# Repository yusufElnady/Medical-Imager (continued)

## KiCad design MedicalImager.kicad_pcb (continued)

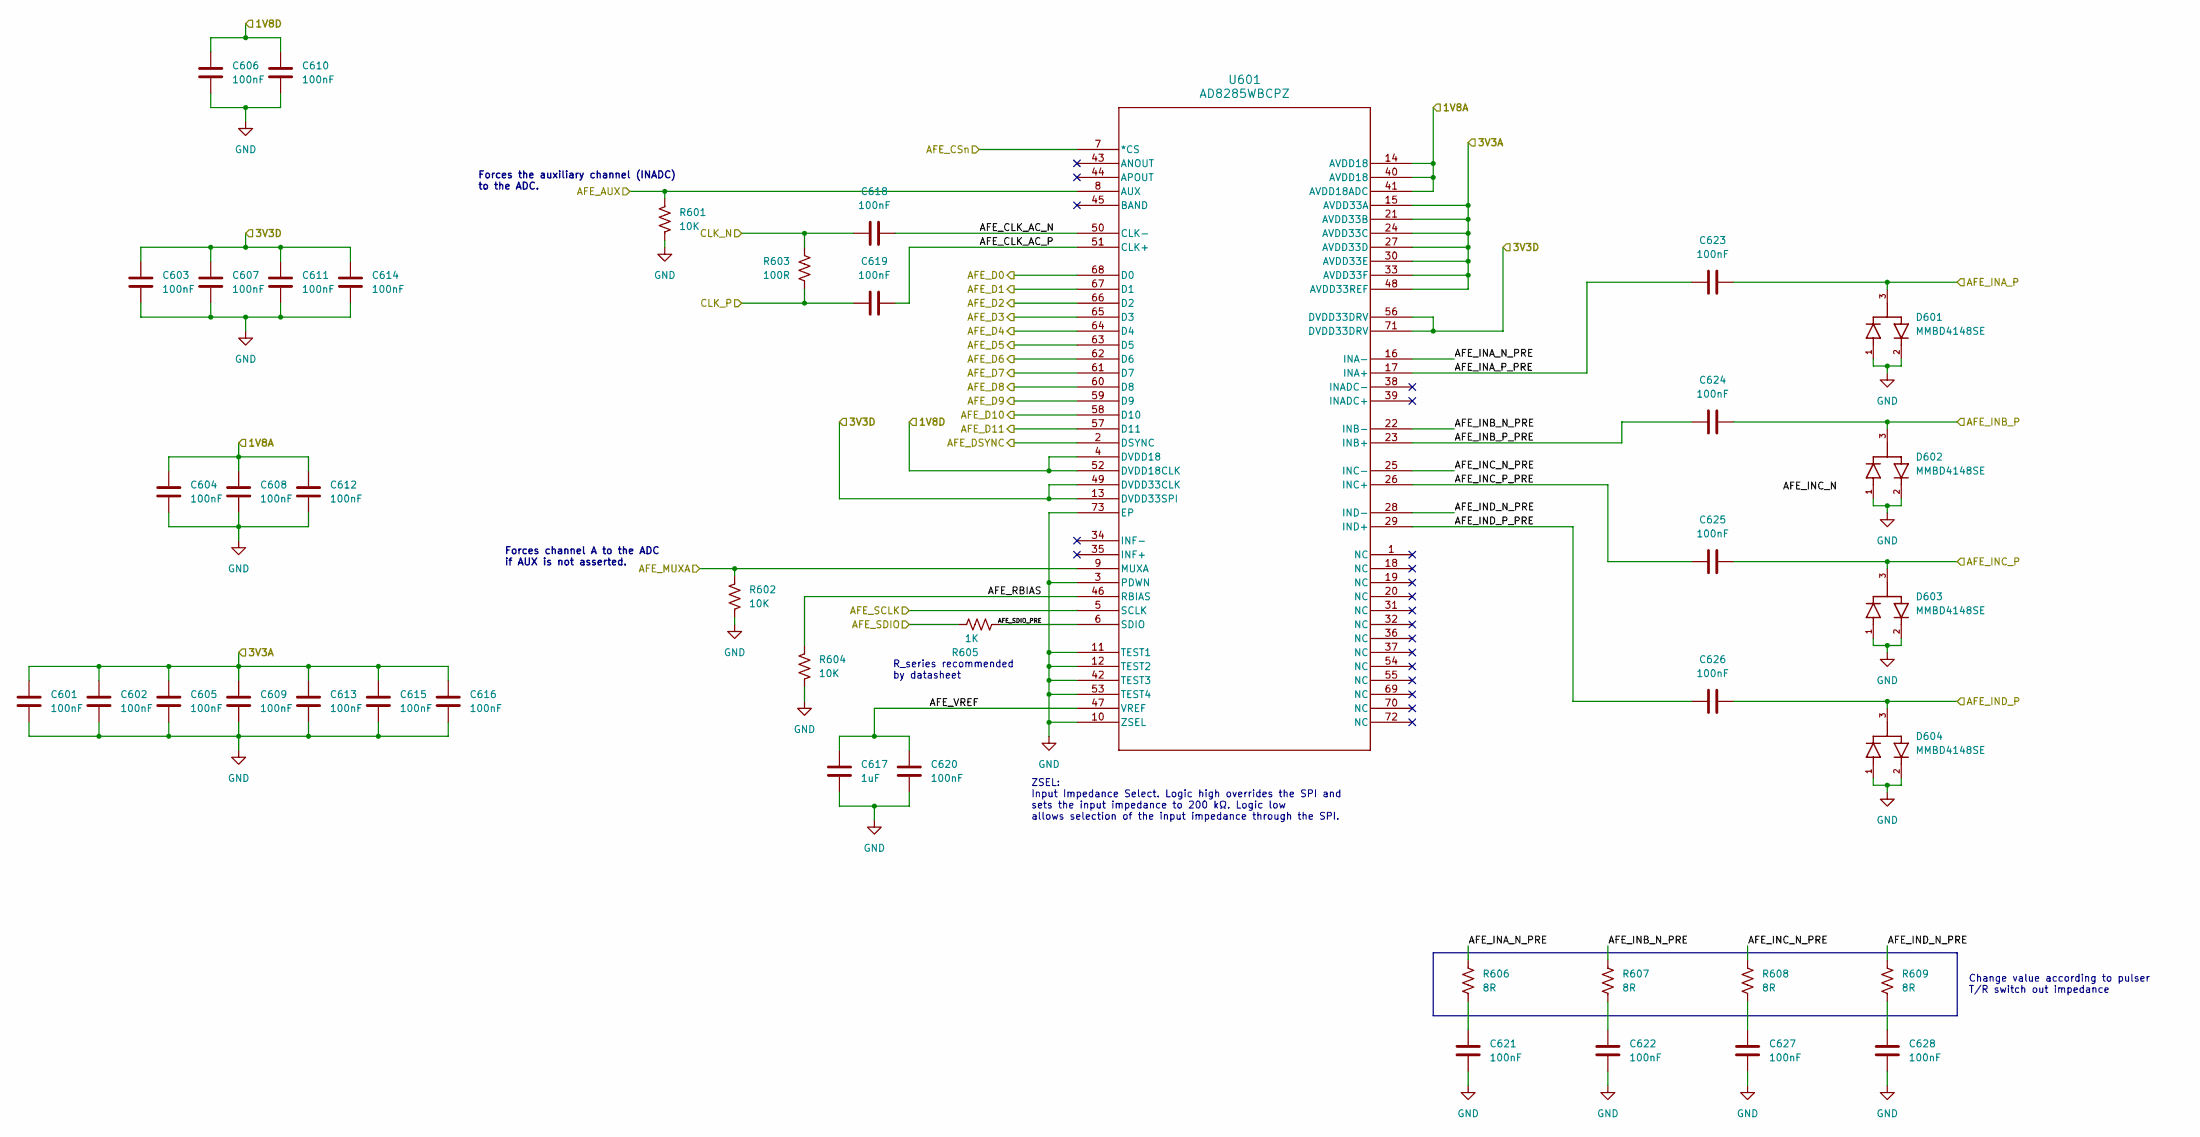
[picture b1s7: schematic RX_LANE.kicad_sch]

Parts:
C601, C602, C603, C604, C605, C606, C607, C608, C609, C610, C611, C612, C613, C614, C615, C616, C618, C619, C620, C621, C622, C623, C624, C625, C626, C627, C628: 100nF; C_0402_1005Metric
C617: 1uF; C_0402_1005Metric
D601, D602, D603, D604: MMBD4148SE; SOT95P237X112-3N; PARTREV E2001
R601, R602, R604: 10K; R_0402_1005Metric
R603: 100R; R_0402_1005Metric
R605: 1K; R_0402_1005Metric
R606, R607, R608, R609: 8R; R_0402_1005Metric
U601: AD8285WBCPZ; CP_72_5_ADI

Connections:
/RX/AFE1/AFE_CLK_AC_N: C618.2, U601.50 (CLK-)
/RX/AFE1/AFE_CLK_AC_P: C619.2, U601.51 (CLK+)
/RX/AFE1/AFE_INA_N_PRE: R606.1, U601.16 (INA-)
/RX/AFE1/AFE_INA_P_PRE: C623.2, U601.17 (INA+)
/RX/AFE1/AFE_INB_N_PRE: R607.1, U601.22 (INB-)
/RX/AFE1/AFE_INB_P_PRE: C624.2, U601.23 (INB+)
/RX/AFE1/AFE_INC_N_PRE: R608.1, U601.25 (INC-)
/RX/AFE1/AFE_INC_P_PRE: C625.2, U601.26 (INC+)
/RX/AFE1/AFE_IND_N_PRE: R609.1, U601.28 (IND-)
/RX/AFE1/AFE_IND_P_PRE: C626.2, U601.29 (IND+)
/RX/AFE1/AFE_RBIAS: R604.1, U601.46 (RBIAS)
/RX/AFE1/AFE_SDIO_PRE: R605.2, U601.6 (SDIO)
/RX/AFE1/AFE_VREF: C617.1, C620.1, U601.47 (VREF)
/RX/AFE1_AUX: R601.1, U601.8 (AUX); also elsewhere on the board
/RX/AFE1_CSn: U601.7 (*CS); also elsewhere on the board
/RX/AFE1_DSYNC: U601.2 (DSYNC); also elsewhere on the board
/RX/AFE1_MUXA: R602.1, U601.9 (MUXA); also elsewhere on the board
/RX/AFE_OUTPUTS0: U601.68 (D0); also elsewhere on the board
/RX/AFE_OUTPUTS1: U601.67 (D1); also elsewhere on the board
/RX/AFE_OUTPUTS2: U601.66 (D2); also elsewhere on the board
/RX/AFE_OUTPUTS3: U601.65 (D3); also elsewhere on the board
/RX/AFE_OUTPUTS4: U601.64 (D4); also elsewhere on the board
/RX/AFE_OUTPUTS5: U601.63 (D5); also elsewhere on the board
/RX/AFE_OUTPUTS6: U601.62 (D6); also elsewhere on the board
/RX/AFE_OUTPUTS7: U601.61 (D7); also elsewhere on the board
/RX/AFE_OUTPUTS8: U601.60 (D8); also elsewhere on the board
/RX/AFE_OUTPUTS9: U601.59 (D9); also elsewhere on the board
/RX/AFE_OUTPUTS10: U601.58 (D10); also elsewhere on the board
/RX/AFE_OUTPUTS11: U601.57 (D11); also elsewhere on the board
/RX/AFE_SCLK: U601.5 (SCLK); also elsewhere on the board
/RX/AFE_SDIO: R605.1; also elsewhere on the board
/RX/CLKOUT_B1_N: C618.1, R603.1; also elsewhere on the board
/RX/CLKOUT_B1_P: C619.1, R603.2; also elsewhere on the board
/RX/TR_OUT0: C623.1, D601.3; also elsewhere on the board
/RX/TR_OUT1: C624.1, D602.3; also elsewhere on the board
/RX/TR_OUT2: C625.1, D603.3; also elsewhere on the board
/RX/TR_OUT3: C626.1, D604.3; also elsewhere on the board
AFE1_1V8A: C604.1, C608.1, C612.1, U601.14 (AVDD18), U601.40 (AVDD18), U601.41 (AVDD18ADC); also elsewhere on the board
AFE1_1V8D: C606.1, C610.1, U601.4 (DVDD18), U601.52 (DVDD18CLK); also elsewhere on the board
AFE1_3V3A: C601.1, C602.1, C605.1, C609.1, C613.1, C615.1, C616.1, U601.15 (AVDD33A), U601.21 (AVDD33B), U601.24 (AVDD33C), U601.27 (AVDD33D), U601.30 (AVDD33E), U601.33 (AVDD33F), U601.48 (AVDD33REF); also elsewhere on the board
AFE1_3V3D: C603.1, C607.1, C611.1, C614.1, U601.13 (DVDD33SPI), U601.49 (DVDD33CLK), U601.56 (DVDD33DRV), U601.71 (DVDD33DRV); also elsewhere on the board
GND: C601.2, C602.2, C603.2, C604.2, C605.2, C606.2, C607.2, C608.2, C609.2, C610.2, C611.2, C612.2, C613.2, C614.2, C615.2, C616.2, C617.2, C620.2, C621.2, C622.2, C627.2, C628.2, D601.1, D601.2, D602.1, D602.2, D603.1, D603.2, D604.1, D604.2, R601.2, R602.2, R604.2, U601.3 (PDWN), U601.10 (ZSEL), U601.11 (TEST1), U601.12 (TEST2), U601.42 (TEST3), U601.53 (TEST4), U601.73 (EP); also elsewhere on the board
unnamed: C621.1, R606.2
unnamed: C622.1, R607.2
unnamed: C627.1, R608.2
unnamed: C628.1, R609.2

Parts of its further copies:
C701, C702, C703, C704, C705, C706, C707, C708, C709, C710, C711, C712, C713, C714, C715, C716, C718, C719, C720, C721, C722, C723, C724, C725, C726, C727, C728, C801, C802, C803, C804, C805, C806, C807, C808, C809, C810, C811, C812, C813, C814, C815, C816, C818, C819, C820, C821, C822, C823, C824, C825, C826, C827, C828, C901, C902, C903, C904, C905, C906, C907, C908, C909, C910, C911, C912, C913, C914, C915, C916, C918, C919, C920, C921, C922, C923, C924, C925, C926, C927, C928: 100nF; C_0402_1005Metric
C717, C817, C917: 1uF; C_0402_1005Metric
D701, D702, D703, D704, D801, D802, D803, D804, D901, D902, D903, D904: MMBD4148SE; SOT95P237X112-3N; PARTREV E2001
R701, R702, R704, R801, R802, R804, R901, R902, R904: 10K; R_0402_1005Metric
R703, R803, R903: 100R; R_0402_1005Metric
R705, R805, R905: 1K; R_0402_1005Metric
R706, R707, R708, R709, R806, R807, R808, R809, R906, R907, R908, R909: 8R; R_0402_1005Metric
U701, U801, U901: AD8285WBCPZ; CP_72_5_ADI

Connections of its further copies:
/RX/AFE2/AFE_CLK_AC_N: C718.2, U701.50 (CLK-)
/RX/AFE2/AFE_CLK_AC_P: C719.2, U701.51 (CLK+)
/RX/AFE2/AFE_INA_N_PRE: R706.1, U701.16 (INA-)
/RX/AFE2/AFE_INA_P_PRE: C723.2, U701.17 (INA+)
/RX/AFE2/AFE_INB_N_PRE: R707.1, U701.22 (INB-)
/RX/AFE2/AFE_INB_P_PRE: C724.2, U701.23 (INB+)
/RX/AFE2/AFE_INC_N_PRE: R708.1, U701.25 (INC-)
/RX/AFE2/AFE_INC_P_PRE: C725.2, U701.26 (INC+)
/RX/AFE2/AFE_IND_N_PRE: R709.1, U701.28 (IND-)
/RX/AFE2/AFE_IND_P_PRE: C726.2, U701.29 (IND+)
/RX/AFE2/AFE_RBIAS: R704.1, U701.46 (RBIAS)
/RX/AFE2/AFE_SDIO_PRE: R705.2, U701.6 (SDIO)
/RX/AFE2/AFE_VREF: C717.1, C720.1, U701.47 (VREF)
/RX/AFE2_AUX: R701.1, U701.8 (AUX); also elsewhere on the board
/RX/AFE2_CSn: U701.7 (*CS); also elsewhere on the board
/RX/AFE2_DSYNC: U701.2 (DSYNC); also elsewhere on the board
/RX/AFE2_MUXA: R702.1, U701.9 (MUXA); also elsewhere on the board
/RX/AFE3/AFE_CLK_AC_N: C818.2, U801.50 (CLK-)
/RX/AFE3/AFE_CLK_AC_P: C819.2, U801.51 (CLK+)
/RX/AFE3/AFE_INA_N_PRE: R806.1, U801.16 (INA-)
/RX/AFE3/AFE_INA_P_PRE: C823.2, U801.17 (INA+)
/RX/AFE3/AFE_INB_N_PRE: R807.1, U801.22 (INB-)
/RX/AFE3/AFE_INB_P_PRE: C824.2, U801.23 (INB+)
/RX/AFE3/AFE_INC_N_PRE: R808.1, U801.25 (INC-)
/RX/AFE3/AFE_INC_P_PRE: C825.2, U801.26 (INC+)
/RX/AFE3/AFE_IND_N_PRE: R809.1, U801.28 (IND-)
/RX/AFE3/AFE_IND_P_PRE: C826.2, U801.29 (IND+)
/RX/AFE3/AFE_RBIAS: R804.1, U801.46 (RBIAS)
/RX/AFE3/AFE_SDIO_PRE: R805.2, U801.6 (SDIO)
/RX/AFE3/AFE_VREF: C817.1, C820.1, U801.47 (VREF)
/RX/AFE3_AUX: R801.1, U801.8 (AUX); also elsewhere on the board
/RX/AFE3_CSn: U801.7 (*CS); also elsewhere on the board
/RX/AFE3_DSYNC: U801.2 (DSYNC); also elsewhere on the board
/RX/AFE3_MUXA: R802.1, U801.9 (MUXA); also elsewhere on the board
/RX/AFE4/AFE_CLK_AC_N: C918.2, U901.50 (CLK-)
/RX/AFE4/AFE_CLK_AC_P: C919.2, U901.51 (CLK+)
/RX/AFE4/AFE_INA_N_PRE: R906.1, U901.16 (INA-)
/RX/AFE4/AFE_INA_P_PRE: C923.2, U901.17 (INA+)
/RX/AFE4/AFE_INB_N_PRE: R907.1, U901.22 (INB-)
/RX/AFE4/AFE_INB_P_PRE: C924.2, U901.23 (INB+)
/RX/AFE4/AFE_INC_N_PRE: R908.1, U901.25 (INC-)
/RX/AFE4/AFE_INC_P_PRE: C925.2, U901.26 (INC+)
/RX/AFE4/AFE_IND_N_PRE: R909.1, U901.28 (IND-)
/RX/AFE4/AFE_IND_P_PRE: C926.2, U901.29 (IND+)
/RX/AFE4/AFE_RBIAS: R904.1, U901.46 (RBIAS)
/RX/AFE4/AFE_SDIO_PRE: R905.2, U901.6 (SDIO)
/RX/AFE4/AFE_VREF: C917.1, C920.1, U901.47 (VREF)
/RX/AFE4_AUX: R901.1, U901.8 (AUX); also elsewhere on the board
/RX/AFE4_CSn: U901.7 (*CS); also elsewhere on the board
/RX/AFE4_DSYNC: U901.2 (DSYNC); also elsewhere on the board
/RX/AFE4_MUXA: R902.1, U901.9 (MUXA); also elsewhere on the board
/RX/AFE_OUTPUTS12: U701.68 (D0); also elsewhere on the board
/RX/AFE_OUTPUTS13: U701.67 (D1); also elsewhere on the board
/RX/AFE_OUTPUTS14: U701.66 (D2); also elsewhere on the board
/RX/AFE_OUTPUTS15: U701.65 (D3); also elsewhere on the board
/RX/AFE_OUTPUTS16: U701.64 (D4); also elsewhere on the board
/RX/AFE_OUTPUTS17: U701.63 (D5); also elsewhere on the board
/RX/AFE_OUTPUTS18: U701.62 (D6); also elsewhere on the board
/RX/AFE_OUTPUTS19: U701.61 (D7); also elsewhere on the board
/RX/AFE_OUTPUTS20: U701.60 (D8); also elsewhere on the board
/RX/AFE_OUTPUTS21: U701.59 (D9); also elsewhere on the board
/RX/AFE_OUTPUTS22: U701.58 (D10); also elsewhere on the board
/RX/AFE_OUTPUTS23: U701.57 (D11); also elsewhere on the board
/RX/AFE_OUTPUTS24: U801.68 (D0); also elsewhere on the board
/RX/AFE_OUTPUTS25: U801.67 (D1); also elsewhere on the board
/RX/AFE_OUTPUTS26: U801.66 (D2); also elsewhere on the board
/RX/AFE_OUTPUTS27: U801.65 (D3); also elsewhere on the board
/RX/AFE_OUTPUTS28: U801.64 (D4); also elsewhere on the board
/RX/AFE_OUTPUTS29: U801.63 (D5); also elsewhere on the board
/RX/AFE_OUTPUTS30: U801.62 (D6); also elsewhere on the board
/RX/AFE_OUTPUTS31: U801.61 (D7); also elsewhere on the board
/RX/AFE_OUTPUTS32: U801.60 (D8); also elsewhere on the board
/RX/AFE_OUTPUTS33: U801.59 (D9); also elsewhere on the board
/RX/AFE_OUTPUTS34: U801.58 (D10); also elsewhere on the board
/RX/AFE_OUTPUTS35: U801.57 (D11); also elsewhere on the board
/RX/AFE_OUTPUTS36: U901.68 (D0); also elsewhere on the board
/RX/AFE_OUTPUTS37: U901.67 (D1); also elsewhere on the board
/RX/AFE_OUTPUTS38: U901.66 (D2); also elsewhere on the board
/RX/AFE_OUTPUTS39: U901.65 (D3); also elsewhere on the board
/RX/AFE_OUTPUTS40: U901.64 (D4); also elsewhere on the board
/RX/AFE_OUTPUTS41: U901.63 (D5); also elsewhere on the board
/RX/AFE_OUTPUTS42: U901.62 (D6); also elsewhere on the board
/RX/AFE_OUTPUTS43: U901.61 (D7); also elsewhere on the board
/RX/AFE_OUTPUTS44: U901.60 (D8); also elsewhere on the board
/RX/AFE_OUTPUTS45: U901.59 (D9); also elsewhere on the board
/RX/AFE_OUTPUTS46: U901.58 (D10); also elsewhere on the board
/RX/AFE_OUTPUTS47: U901.57 (D11); also elsewhere on the board
/RX/AFE_SCLK: U701.5 (SCLK), U801.5 (SCLK), U901.5 (SCLK); also elsewhere on the board
/RX/AFE_SDIO: R705.1, R805.1, R905.1; also elsewhere on the board
/RX/CLKOUT_A0_N: C918.1, R903.1; also elsewhere on the board
/RX/CLKOUT_A0_P: C919.1, R903.2; also elsewhere on the board
/RX/CLKOUT_A1_N: C818.1, R803.1; also elsewhere on the board
/RX/CLKOUT_A1_P: C819.1, R803.2; also elsewhere on the board
/RX/CLKOUT_B0_N: C718.1, R703.1; also elsewhere on the board
/RX/CLKOUT_B0_P: C719.1, R703.2; also elsewhere on the board
/RX/TR_OUT4: C723.1, D701.3; also elsewhere on the board
/RX/TR_OUT5: C724.1, D702.3; also elsewhere on the board
/RX/TR_OUT6: C725.1, D703.3; also elsewhere on the board
/RX/TR_OUT7: C726.1, D704.3; also elsewhere on the board
/RX/TR_OUT8: C823.1, D801.3; also elsewhere on the board
/RX/TR_OUT9: C824.1, D802.3; also elsewhere on the board
/RX/TR_OUT10: C825.1, D803.3; also elsewhere on the board
/RX/TR_OUT11: C826.1, D804.3; also elsewhere on the board
/RX/TR_OUT12: C923.1, D901.3; also elsewhere on the board
/RX/TR_OUT13: C924.1, D902.3; also elsewhere on the board
/RX/TR_OUT14: C925.1, D903.3; also elsewhere on the board
/RX/TR_OUT15: C926.1, D904.3; also elsewhere on the board
AFE1_1V8D: C706.1, C710.1, U701.4 (DVDD18), U701.52 (DVDD18CLK); also elsewhere on the board
AFE1_3V3D: C703.1, C707.1, C711.1, C714.1, U701.13 (DVDD33SPI), U701.49 (DVDD33CLK), U701.56 (DVDD33DRV), U701.71 (DVDD33DRV); also elsewhere on the board
AFE2_1V8A: C704.1, C708.1, C712.1, U701.14 (AVDD18), U701.40 (AVDD18), U701.41 (AVDD18ADC); also elsewhere on the board
AFE2_3V3A: C701.1, C702.1, C705.1, C709.1, C713.1, C715.1, C716.1, U701.15 (AVDD33A), U701.21 (AVDD33B), U701.24 (AVDD33C), U701.27 (AVDD33D), U701.30 (AVDD33E), U701.33 (AVDD33F), U701.48 (AVDD33REF); also elsewhere on the board
AFE3_1V8A: C804.1, C808.1, C812.1, U801.14 (AVDD18), U801.40 (AVDD18), U801.41 (AVDD18ADC); also elsewhere on the board
AFE3_1V8D: C806.1, C810.1, C906.1, C910.1, U801.4 (DVDD18), U801.52 (DVDD18CLK), U901.4 (DVDD18), U901.52 (DVDD18CLK); also elsewhere on the board
AFE3_3V3A: C801.1, C802.1, C805.1, C809.1, C813.1, C815.1, C816.1, U801.15 (AVDD33A), U801.21 (AVDD33B), U801.24 (AVDD33C), U801.27 (AVDD33D), U801.30 (AVDD33E), U801.33 (AVDD33F), U801.48 (AVDD33REF); also elsewhere on the board
AFE3_3V3D: C803.1, C807.1, C811.1, C814.1, C903.1, C907.1, C911.1, C914.1, U801.13 (DVDD33SPI), U801.49 (DVDD33CLK), U801.56 (DVDD33DRV), U801.71 (DVDD33DRV), U901.13 (DVDD33SPI), U901.49 (DVDD33CLK), U901.56 (DVDD33DRV), U901.71 (DVDD33DRV); also elsewhere on the board
AFE4_1V8A: C904.1, C908.1, C912.1, U901.14 (AVDD18), U901.40 (AVDD18), U901.41 (AVDD18ADC); also elsewhere on the board
AFE4_3V3A: C901.1, C902.1, C905.1, C909.1, C913.1, C915.1, C916.1, U901.15 (AVDD33A), U901.21 (AVDD33B), U901.24 (AVDD33C), U901.27 (AVDD33D), U901.30 (AVDD33E), U901.33 (AVDD33F), U901.48 (AVDD33REF); also elsewhere on the board
GND: C701.2, C702.2, C703.2, C704.2, C705.2, C706.2, C707.2, C708.2, C709.2, C710.2, C711.2, C712.2, C713.2, C714.2, C715.2, C716.2, C717.2, C720.2, C721.2, C722.2, C727.2, C728.2, C801.2, C802.2, C803.2, C804.2, C805.2, C806.2, C807.2, C808.2, C809.2, C810.2, C811.2, C812.2, C813.2, C814.2, C815.2, C816.2, C817.2, C820.2, C821.2, C822.2, C827.2, C828.2, C901.2, C902.2, C903.2, C904.2, C905.2, C906.2, C907.2, C908.2, C909.2, C910.2, C911.2, C912.2, C913.2, C914.2, C915.2, C916.2, C917.2, C920.2, C921.2, C922.2, C927.2, C928.2, D701.1, D701.2, D702.1, D702.2, D703.1, D703.2, D704.1, D704.2, D801.1, D801.2, D802.1, D802.2, D803.1, D803.2, D804.1, D804.2, D901.1, D901.2, D902.1, D902.2, D903.1, D903.2, D904.1, D904.2, R701.2, R702.2, R704.2, R801.2, R802.2, R804.2, R901.2, R902.2, R904.2, U701.3 (PDWN), U701.10 (ZSEL), U701.11 (TEST1), U701.12 (TEST2), U701.42 (TEST3), U701.53 (TEST4), U701.73 (EP), U801.3 (PDWN), U801.10 (ZSEL), U801.11 (TEST1), U801.12 (TEST2), U801.42 (TEST3), U801.53 (TEST4), U801.73 (EP), U901.3 (PDWN), U901.10 (ZSEL), U901.11 (TEST1), U901.12 (TEST2), U901.42 (TEST3), U901.53 (TEST4), U901.73 (EP); also elsewhere on the board
unnamed: C721.1, R706.2
unnamed: C722.1, R707.2
unnamed: C727.1, R708.2
unnamed: C728.1, R709.2
unnamed: C821.1, R806.2
unnamed: C822.1, R807.2
unnamed: C827.1, R808.2
unnamed: C828.1, R809.2
unnamed: C921.1, R906.2
unnamed: C922.1, R907.2
unnamed: C927.1, R908.2
unnamed: C928.1, R909.2

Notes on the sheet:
ZSEL: Input Impedance Select. Logic high overrides the SPI and sets the input impedance to 200 kΩ. Logic low allows selection of the input impedance through the SPI.
Forces channel A to the ADC if AUX is not asserted.
R_series recommended by datasheet
Change value according to pulser T/R switch out impedance
Forces the auxiliary channel (INADC) to the ADC.

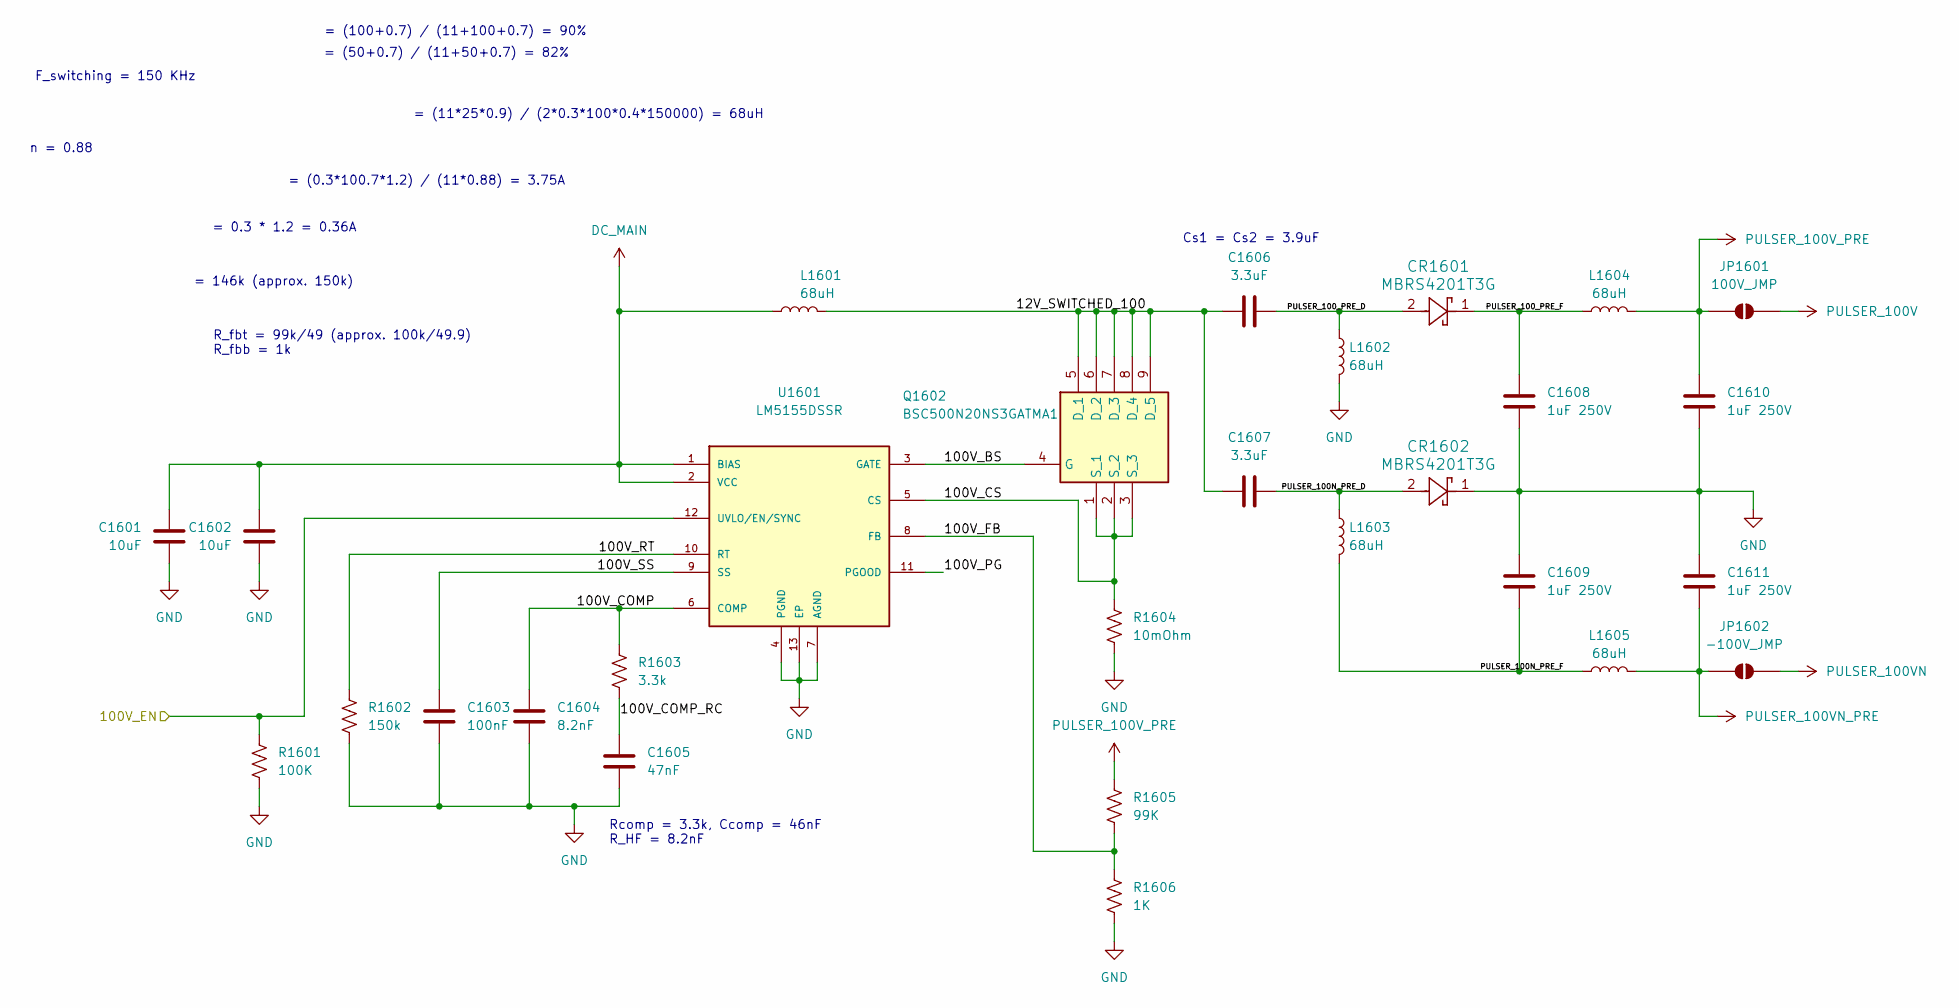
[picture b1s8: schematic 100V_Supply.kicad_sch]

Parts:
C1601, C1602: 10uF; C_0805_2012Metric
C1603: 100nF; C_0402_1005Metric
C1604: 8.2nF; C_0402_1005Metric
C1605: 47nF; C_0402_1005Metric
C1606, C1607: 3.3uF; C_2220_5750Metric
C1608, C1609, C1610, C1611: 1uF 250V; C_1812_4532Metric
CR1601, CR1602: MBRS4201T3G; SDO_SMC-2_403AC-B_OSI
JP1601: 100V_JMP; SolderJumper-2_P1.3mm_Open_TrianglePad1.0x1.5mm
JP1602: -100V_JMP; SolderJumper-2_P1.3mm_Open_TrianglePad1.0x1.5mm
L1601: 68uH; L_Panasonic_PCC-M0854M
L1602, L1603, L1604, L1605: 68uH; L_Cenker_CKCS4018
Q1602: BSC500N20NS3GATMA1; Manufacturer_Part_Number BSC500N20NS3GATMA1; Mouser Part Number 726-BSC500N20NS3GATM
R1601: 100K; R_0402_1005Metric
R1602: 150k; R_0402_1005Metric
R1603: 3.3k; R_0402_1005Metric
R1604: 10mOhm; R_0603_1608Metric
R1605: 99K; R_0402_1005Metric
R1606: 1K; R_0402_1005Metric
U1601: LM5155DSSR; IC_LM5155DSSR; PARTREV E

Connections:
/Power/100V_EN: R1601.1, U1601.12 (UVLO/EN/SYNC); also elsewhere on the board
/Power/100V_SUPPLY/12V_SWITCHED_100: C1606.1, C1607.1, L1601.1, Q1602.5 (D_1), Q1602.6 (D_2), Q1602.7 (D_3), Q1602.8 (D_4), Q1602.9 (D_5)
/Power/100V_SUPPLY/100V_BS: Q1602.4 (G), U1601.3 (GATE)
/Power/100V_SUPPLY/100V_COMP: C1604.1, R1603.1, U1601.6 (COMP)
/Power/100V_SUPPLY/100V_COMP_RC: C1605.1, R1603.2
/Power/100V_SUPPLY/100V_CS: Q1602.1 (S_1), Q1602.2 (S_2), Q1602.3 (S_3), R1604.2, U1601.5 (CS)
/Power/100V_SUPPLY/100V_FB: R1605.2, R1606.1, U1601.8 (FB)
/Power/100V_SUPPLY/100V_PG: U1601.11 (PGOOD)
/Power/100V_SUPPLY/100V_RT: R1602.1, U1601.10 (RT)
/Power/100V_SUPPLY/100V_SS: C1603.2, U1601.9 (SS)
/Power/100V_SUPPLY/PULSER_100N_PRE_D: C1607.2, CR1602.2, L1603.1
/Power/100V_SUPPLY/PULSER_100N_PRE_F: C1609.2, L1603.2, L1605.1
/Power/100V_SUPPLY/PULSER_100_PRE_D: C1606.2, CR1601.2, L1602.1
/Power/100V_SUPPLY/PULSER_100_PRE_F: C1608.1, CR1601.1, L1604.1
DC_MAIN: C1601.1, C1602.1, L1601.2, U1601.1 (BIAS), U1601.2 (VCC); also elsewhere on the board
GND: C1601.2, C1602.2, C1603.1, C1604.2, C1605.2, C1608.2, C1609.1, C1610.2, C1611.1, CR1602.1, L1602.2, R1601.2, R1602.2, R1604.1, R1606.2, U1601.4 (PGND), U1601.7 (AGND), U1601.13 (EP); also elsewhere on the board
PULSER_100V: JP1601.2 (B); also elsewhere on the board
PULSER_100VN: JP1602.2 (B); also elsewhere on the board
PULSER_100VN_PRE: C1611.2, JP1602.1 (A), L1605.2
PULSER_100V_PRE: C1610.1, JP1601.1 (A), L1604.2, R1605.1

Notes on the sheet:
F_switching = 150 KHz
Cs1 = Cs2 = 3.9uF
= (100+0.7) / (11+100+0.7) = 90%
Rcomp = 3.3k, Ccomp = 46nF R_HF = 8.2nF
= 146k (approx. 150k)
n = 0.88
= (11*25*0.9) / (2*0.3*100*0.4*150000) = 68uH
= 0.3 * 1.2 = 0.36A
R_fbt = 99k/49 (approx. 100k/49.9) R_fbb = 1k
= (50+0.7) / (11+50+0.7) = 82%
= (0.3*100.7*1.2) / (11*0.88) = 3.75A

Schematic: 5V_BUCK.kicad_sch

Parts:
C1901, C1913: 4.7uF; C_0805_2012Metric
C1902, C1915: 470nF; C_0402_1005Metric
C1907, C1908, C1910: 47uF; C_0805_2012Metric
C1911: 100nF; C_0402_1005Metric
C1912: 1pF; C_0402_1005Metric
C1914: 1uF; C_0402_1005Metric
L1902: 8.2uH; L_10.4x10.4_H4.8
R1901, R1907: 100K; R_0402_1005Metric
R1906: 32.4k; R_0402_1005Metric
R1908: 24.9K; R_0402_1005Metric
U1902: LM61460AANRJRR; IC_LM61460AANRJRR; MPN LM61460AANRJRR

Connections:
/Power/SOM_5V/BUCK_BS: C1911.1, U1902.13 (RBOOT), U1902.14 (CBOOT)
/Power/SOM_5V/BUCK_FB: C1912.2, R1907.2, R1908.1, U1902.4 (FB)
/Power/SOM_5V/BUCK_RT: R1906.1, U1902.6 (RT)
/Power/SOM_5V/BUCK_SW: C1911.2, L1902.1, U1902.10 (SW)
/Power/SOM_5V/BUCK_VCC: C1914.1, U1902.2 (VCC)
/Power/SOM_5V/PG: R1901.2, U1902.5 (PGOOD)
/Power/SOM_5V/PG_VCC: R1901.1
DC_MAIN: C1901.1, C1902.1, C1913.1, C1915.1, U1902.7 (EN/SYNC), U1902.8 (VIN1), U1902.12 (VIN2); also elsewhere on the board
GND: C1901.2, C1902.2, C1907.2, C1908.2, C1910.2, C1913.2, C1914.2, C1915.2, R1906.2, R1908.2, U1902.3 (AGND), U1902.9 (PGND1), U1902.11 (PGND2); also elsewhere on the board
SOM_5V_PRE: C1907.1, C1908.1, C1910.1, C1912.1, L1902.2, R1907.1, U1902.1 (BIAS); also elsewhere on the board

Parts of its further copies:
C2001, C2013: 4.7uF; C_0805_2012Metric
C2002, C2015: 470nF; C_0402_1005Metric
C2007, C2008, C2010: 47uF; C_0805_2012Metric
C2011: 100nF; C_0402_1005Metric
C2012: 1pF; C_0402_1005Metric
C2014: 1uF; C_0402_1005Metric
L2002: 8.2uH; L_10.4x10.4_H4.8
R2001, R2007: 100K; R_0402_1005Metric
R2006: 32.4k; R_0402_1005Metric
R2008: 24.9K; R_0402_1005Metric
U2002: LM61460AANRJRR; IC_LM61460AANRJRR; MPN LM61460AANRJRR

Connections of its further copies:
/Power/IM_5V/BUCK_BS: C2011.1, U2002.13 (RBOOT), U2002.14 (CBOOT)
/Power/IM_5V/BUCK_FB: C2012.2, R2007.2, R2008.1, U2002.4 (FB)
/Power/IM_5V/BUCK_RT: R2006.1, U2002.6 (RT)
/Power/IM_5V/BUCK_SW: C2011.2, L2002.1, U2002.10 (SW)
/Power/IM_5V/BUCK_VCC: C2014.1, U2002.2 (VCC)
/Power/IM_5V/PG: R2001.2, U2002.5 (PGOOD)
/Power/IM_5V/PG_VCC: R2001.1
/Power/IM_5V_EN: U2002.7 (EN/SYNC); also elsewhere on the board
DC_MAIN: C2001.1, C2002.1, C2013.1, C2015.1, U2002.8 (VIN1), U2002.12 (VIN2); also elsewhere on the board
GND: C2001.2, C2002.2, C2007.2, C2008.2, C2010.2, C2013.2, C2014.2, C2015.2, R2006.2, R2008.2, U2002.3 (AGND), U2002.9 (PGND1), U2002.11 (PGND2); also elsewhere on the board
IM_5V_PRE: C2007.1, C2008.1, C2010.1, C2012.1, L2002.2, R2007.1, U2002.1 (BIAS); also elsewhere on the board

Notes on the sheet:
WeBench Designer Link

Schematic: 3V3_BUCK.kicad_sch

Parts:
C1101, C1102: 10uF; C_0805_2012Metric
C1103: 100nF; C_0402_1005Metric
C1104: 56pF; C_0402_1005Metric
C1105: 100uF; C_0805_2012Metric
L1101: 6.8uH; L_6.3x6.3_H3
R1101: 100K; R_0402_1005Metric
R1102: 22K; R_0402_1005Metric
U1101: TPS54302; SOT-23-6

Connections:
/Power/SOM_HDC_3V3/BS: C1103.1, U1101.6 (BOOT)
/Power/SOM_HDC_3V3/FB: C1104.2, R1101.2, R1102.1, U1101.4 (FB)
/Power/SOM_HDC_3V3/SW: C1103.2, L1101.1, U1101.2 (SW)
/Power/SOM_PL_PWR_EN: U1101.5 (EN); also elsewhere on the board
DC_MAIN: C1101.1, C1102.1, U1101.3 (VIN); also elsewhere on the board
GND: C1101.2, C1102.2, C1105.2, R1102.2, U1101.1 (GND); also elsewhere on the board
VDD_HDBC_PRE: C1104.1, C1105.1, L1101.2, R1101.1; also elsewhere on the board

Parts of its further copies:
C1501, C1502, C1801, C1802: 10uF; C_0805_2012Metric
C1503, C1803: 100nF; C_0402_1005Metric
C1504, C1804: 56pF; C_0402_1005Metric
C1505, C1805: 100uF; C_0805_2012Metric
L1501, L1801: 6.8uH; L_6.3x6.3_H3
R1501, R1801: 100K; R_0402_1005Metric
R1502, R1802: 22K; R_0402_1005Metric
U1501, U1801: TPS54302; SOT-23-6

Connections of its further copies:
/Power/SD_3V3_EN: U1801.5 (EN); also elsewhere on the board
/Power/SD_CARD_3V3/BS: C1803.1, U1801.6 (BOOT)
/Power/SD_CARD_3V3/FB: C1804.2, R1801.2, R1802.1, U1801.4 (FB)
/Power/SD_CARD_3V3/SW: C1803.2, L1801.1, U1801.2 (SW)
/Power/SOM_HDA_3V3/BS: C1503.1, U1501.6 (BOOT)
/Power/SOM_HDA_3V3/FB: C1504.2, R1501.2, R1502.1, U1501.4 (FB)
/Power/SOM_HDA_3V3/SW: C1503.2, L1501.1, U1501.2 (SW)
/Power/SOM_PL_PWR_EN: U1501.5 (EN); also elsewhere on the board
DC_MAIN: C1501.1, C1502.1, C1801.1, C1802.1, U1501.3 (VIN), U1801.3 (VIN); also elsewhere on the board
GND: C1501.2, C1502.2, C1505.2, C1801.2, C1802.2, C1805.2, R1502.2, R1802.2, U1501.1 (GND), U1801.1 (GND); also elsewhere on the board
SD_3V3_PRE: C1804.1, C1805.1, L1801.2, R1801.1; also elsewhere on the board
VDD_HDA_PRE: C1504.1, C1505.1, L1501.2, R1501.1; also elsewhere on the board

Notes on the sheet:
WEBENCH DESIGNER LINK (3.3V)

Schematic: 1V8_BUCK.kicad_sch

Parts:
C1301, C1302: 10uF; C_0805_2012Metric
C1303: 100nF; C_0402_1005Metric
C1304: 47pF; C_0402_1005Metric
C1305, C1306: 100uF; C_0805_2012Metric
L1301: 4.7uH; L_6.3x6.3_H3
R1301: 100K; R_0402_1005Metric
R1302: 49.9K; R_0402_1005Metric
U1301: TPS54302; SOT-23-6

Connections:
/Power/USB_1V8/BS: C1303.1, U1301.6 (BOOT)
/Power/USB_1V8/FB: C1304.2, R1301.2, R1302.1, U1301.4 (FB)
/Power/USB_1V8/SW: C1303.2, L1301.1, U1301.2 (SW)
/Power/USB_1V8_EN: U1301.5 (EN); also elsewhere on the board
DC_MAIN: C1301.1, C1302.1, U1301.3 (VIN); also elsewhere on the board
GND: C1301.2, C1302.2, C1305.2, C1306.2, R1302.2, U1301.1 (GND); also elsewhere on the board
USB_1V8_PRE: C1304.1, C1305.1, C1306.1, L1301.2, R1301.1; also elsewhere on the board

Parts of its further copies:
C1701, C1702: 10uF; C_0805_2012Metric
C1703: 100nF; C_0402_1005Metric
C1704: 47pF; C_0402_1005Metric
C1705, C1706: 100uF; C_0805_2012Metric
L1701: 4.7uH; L_6.3x6.3_H3
R1701: 100K; R_0402_1005Metric
R1702: 49.9K; R_0402_1005Metric
U1701: TPS54302; SOT-23-6

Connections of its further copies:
/Power/SOM_HPA_1V8/BS: C1703.1, U1701.6 (BOOT)
/Power/SOM_HPA_1V8/FB: C1704.2, R1701.2, R1702.1, U1701.4 (FB)
/Power/SOM_HPA_1V8/SW: C1703.2, L1701.1, U1701.2 (SW)
/Power/SOM_PL_PWR_EN: U1701.5 (EN); also elsewhere on the board
DC_MAIN: C1701.1, C1702.1, U1701.3 (VIN); also elsewhere on the board
GND: C1701.2, C1702.2, C1705.2, C1706.2, R1702.2, U1701.1 (GND); also elsewhere on the board
VDD_HPA_PRE: C1704.1, C1705.1, C1706.1, L1701.2, R1701.1; also elsewhere on the board

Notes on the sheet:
WEBENCH DESIGNER LINK (1.8V)

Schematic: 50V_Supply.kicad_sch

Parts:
C1401, C1402: 10uF; C_0805_2012Metric
C1403: 100nF; C_0402_1005Metric
C1404: 47nF; C_0402_1005Metric
C1405: 300nF; C_0402_1005Metric
C1406: 2.2uF 100V; C_0805_2012Metric
C1407: 2.2uF 100v; C_0805_2012Metric
C1408, C1409, C1410, C1411: 1uF 250V; C_1812_4532Metric
CR1401, CR1402: MBRS4201T3G; SDO_SMC-2_403AC-B_OSI
JP1401: 50V_JMP; SolderJumper-2_P1.3mm_Open_TrianglePad1.0x1.5mm
JP1402: -50V_JMP; SolderJumper-2_P1.3mm_Open_TrianglePad1.0x1.5mm
L1401: 150uH; L_SXN_SMDRI127
L1402, L1403: 150uH; L_Cenker_CKCS4018
L1404, L1405: 68uH; L_1210_3225Metric
Q1401: BSC500N20NS3GATMA1; Manufacturer_Part_Number BSC500N20NS3GATMA1; Mouser Part Number 726-BSC500N20NS3GATM
R1401: 100K; R_0402_1005Metric
R1402: 150k; R_0402_1005Metric
R1403: 570R; R_0402_1005Metric
R1404: 10mOhm; R_0603_1608Metric
R1405: 49.9K; R_0402_1005Metric
R1406: 1K; R_0402_1005Metric
U1401: LM5155DSSR; IC_LM5155DSSR; PARTREV E

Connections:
/Power/50V_EN: R1401.1, U1401.12 (UVLO/EN/SYNC); also elsewhere on the board
/Power/50V_SUPPLY/12V_SWITCHED_50: C1406.1, C1407.1, L1401.2, Q1401.5 (D_1), Q1401.6 (D_2), Q1401.7 (D_3), Q1401.8 (D_4), Q1401.9 (D_5)
/Power/50V_SUPPLY/50V_BS: Q1401.4 (G), U1401.3 (GATE)
/Power/50V_SUPPLY/50V_COMP: C1404.1, R1403.1, U1401.6 (COMP)
/Power/50V_SUPPLY/50V_COMP_RC: C1405.1, R1403.2
/Power/50V_SUPPLY/50V_CS: Q1401.1 (S_1), Q1401.2 (S_2), Q1401.3 (S_3), R1404.2, U1401.5 (CS)
/Power/50V_SUPPLY/50V_FB: R1405.2, R1406.1, U1401.8 (FB)
/Power/50V_SUPPLY/50V_PG: U1401.11 (PGOOD)
/Power/50V_SUPPLY/50V_RT: R1402.1, U1401.10 (RT)
/Power/50V_SUPPLY/50V_SS: C1403.2, U1401.9 (SS)
/Power/50V_SUPPLY/PULSER_50N_PRE_D: C1407.2, CR1402.2, L1403.1
/Power/50V_SUPPLY/PULSER_50N_PRE_F: C1409.2, L1403.2, L1405.1
/Power/50V_SUPPLY/PULSER_50_PRE_D: C1406.2, CR1401.2, L1402.1
/Power/50V_SUPPLY/PULSER_50_PRE_F: C1408.1, CR1401.1, L1404.1
DC_MAIN: C1401.1, C1402.1, L1401.1, U1401.1 (BIAS), U1401.2 (VCC); also elsewhere on the board
GND: C1401.2, C1402.2, C1403.1, C1404.2, C1405.2, C1408.2, C1409.1, C1410.2, C1411.1, CR1402.1, L1402.2, R1401.2, R1402.2, R1404.1, R1406.2, U1401.4 (PGND), U1401.7 (AGND), U1401.13 (EP); also elsewhere on the board
PULSER_50V: JP1401.2 (B); also elsewhere on the board
PULSER_50VN: JP1402.2 (B); also elsewhere on the board
PULSER_50VN_PRE: C1411.2, JP1402.1 (A), L1405.2
PULSER_50V_PRE: C1410.1, JP1401.1 (A), L1404.2, R1405.1

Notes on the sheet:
= (100+0.7) / (11+100+0.7) = 90%
F_switching = 150 KHz
R_fbt = 99k/49 (approx. 100k/49.9) R_fbb = 1k
= 146k (approx. 150k)
= 0.3 * 1.2 = 0.36A
Cs1 = Cs2 = 2.2uF
= (0.3*100.7*1.2) / (11*0.88) = 3.75A
= (50+0.7) / (11+50+0.7) = 82%
= (11*25*0.82) / (2*0.3*50*0.4*150000) = 150uH
n = 0.88
Rcomp = 570, Ccomp = 300nF R_HF = 47nF
